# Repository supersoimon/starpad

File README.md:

# StarPad
StarPad is a Star Wars themed macropad with 4 keys, an OLED screen, a rotary encoder, and runs on QMK.

# Features
StarPad features:
- 4 keys
- 128 x 32 OLED screen
- Rotary Encoder (EC11)
- 4-layer PCB Case

# CAD
Here is the CAD design. It consists of 4 different layers (bottom, main, in between - holds keys together?, and top)
It uses m3 screws and heatset inserts to stay attached. There are two screws holding the PCB down, and 2 screws holding the case together.

# PCB Design
My PCB has a couple parts to it - a Seedo Xiao RP 2040, 4 keyswitches, an OLED screen, a rotary encoder, and 4 diodes.

# Software
I use QMK for this project. The 4 keys control up, down, left, and right movement. The rotary encoder controls volume (haven't coded push yet), and the OLED isn't coded either, but I'm planning on adding a cool Star Wars design.

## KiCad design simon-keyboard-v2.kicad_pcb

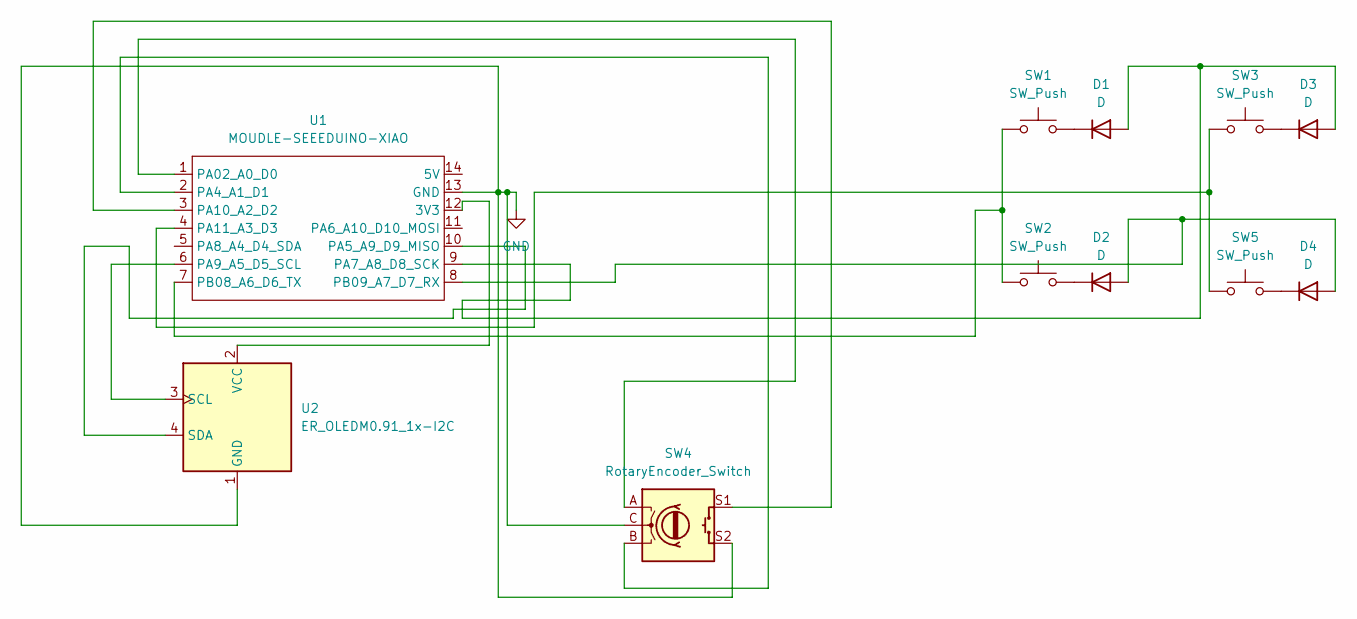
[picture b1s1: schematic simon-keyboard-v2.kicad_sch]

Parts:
D1, D2, D3, D4: D; D_DO-35_SOD27_P7.62mm_Horizontal
SW1, SW2, SW3, SW5: SW_Push; SW_Cherry_MX_1.00u_PCB
SW4: RotaryEncoder_Switch; RotaryEncoder_Alps_EC11E-Switch_Vertical_H20mm
U1: MOUDLE-SEEEDUINO-XIAO; XIAO-Generic-Hybrid-14P-2.54-21X17.8MM
U2: ER_OLEDM0.91_1x-I2C

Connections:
GND: SW4.C, SW4.S2, U1.13 (GND), U2.1 (GND)
unnamed: D1.2 (A), D3.2 (A), U1.9 (PA7_A8_D8_SCK)
unnamed: D1.1 (K), SW1.2
unnamed: D2.2 (A), D4.2 (A), U1.8 (PB09_A7_D7_RX)
unnamed: D2.1 (K), SW2.2
unnamed: D3.1 (K), SW3.2
unnamed: D4.1 (K), SW5.2
unnamed: U1.12 (3V3), U2.2 (VCC)
unnamed: SW4.A, U1.1 (PA02_A0_D0)
unnamed: SW4.B, U1.2 (PA4_A1_D1)
unnamed: U1.10 (PA5_A9_D9_MISO), U2.4 (SDA)
unnamed: U1.6 (PA9_A5_D5_SCL), U2.3 (SCL)
unnamed: SW4.S1, U1.3 (PA10_A2_D2)
unnamed: SW3.1, SW5.1, U1.4 (PA11_A3_D3)
unnamed: SW1.1, SW2.1, U1.7 (PB08_A6_D6_TX)

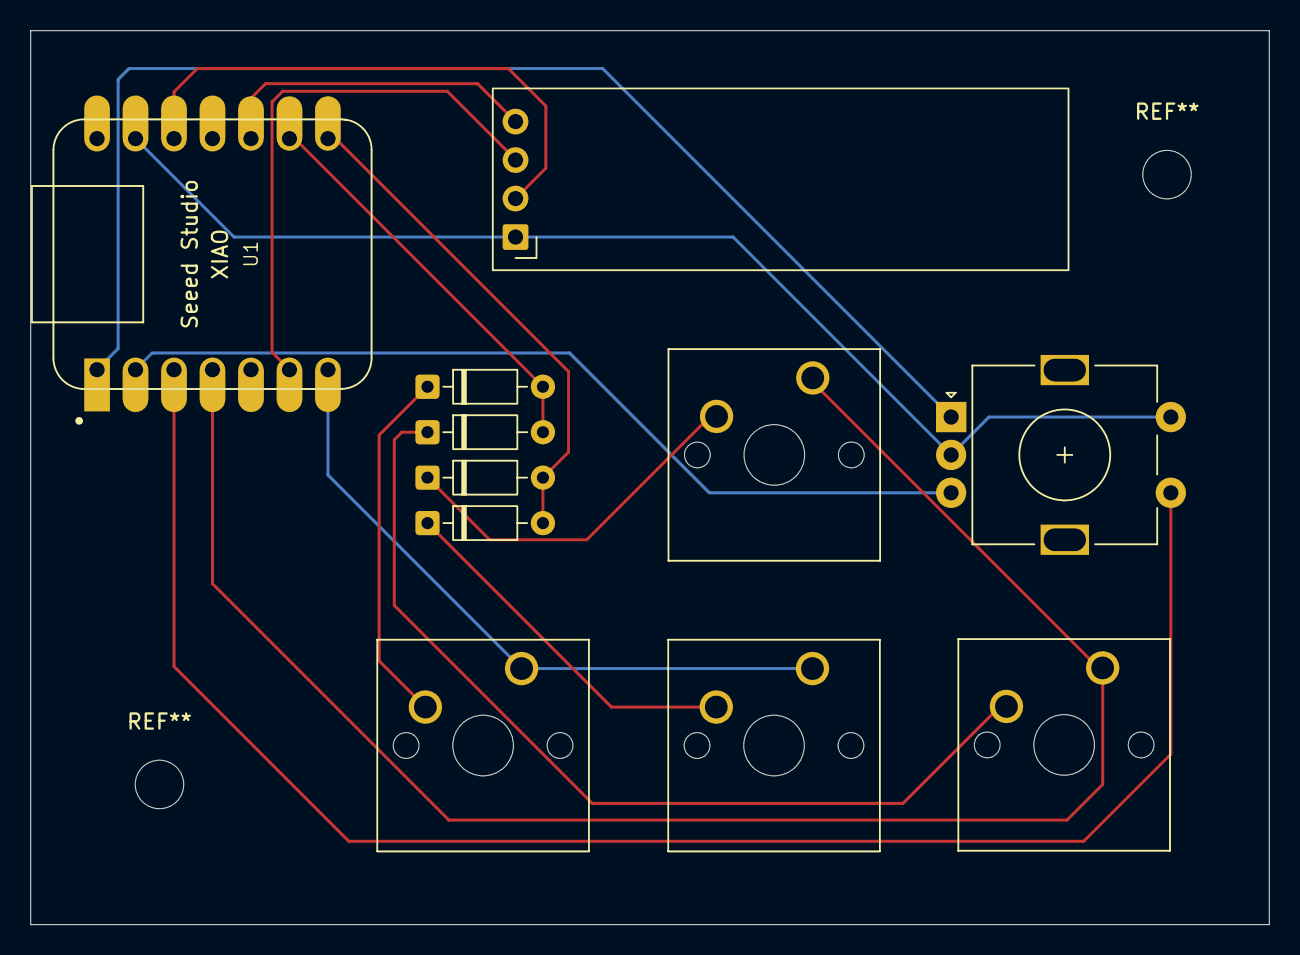
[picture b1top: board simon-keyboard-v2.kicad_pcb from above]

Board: 2 copper layers, 81.8 x 59.0 mm, 11 parts (0 on the bottom side), 15 nets.
